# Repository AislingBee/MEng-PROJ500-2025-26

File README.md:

# MEng-PROJ500-2025-26

Main repository for the PROJ500 humanoid robot project.

Project timeline: December 2025 to May 2026.

## Start Here

1. Read this file for the project map.
2. Read [README_PROJECT_MAP.md](README_PROJECT_MAP.md) for a top-level file/folder map.
3. Read [README_IMPORTANT_PATHS.md](README_IMPORTANT_PATHS.md) for key entrypoints and files.
4. Read [README_QUICKSTART.md](README_QUICKSTART.md) for launch order and runtime checks.
5. For simulation and Isaac workflow, read [simulation/README.md](simulation/README.md).
6. For ROS2 motor stack, read [Software/src/motor_control/README.md](Software/src/motor_control/README.md).
7. For the RCU UDP protocol handover, read [Charlie/STM32Cube/Tools/ROS2/HANDOVER_INSTRUCTIONS.md](Charlie/STM32Cube/Tools/ROS2/HANDOVER_INSTRUCTIONS.md).

## Top-Level Repository Overview

## New STM32 Addition (RCU UDP Bridge)

The current hardware path now supports a direct STM32 RCU UDP binary bridge.

- New bridge node: [Software/src/motor_control/motor_control/bridges/rcu_udp_bridge.py](Software/src/motor_control/motor_control/bridges/rcu_udp_bridge.py)
- RCU launch entrypoint: [Software/src/motor_control/launch/rcu_launch.py](Software/src/motor_control/launch/rcu_launch.py)
- Full RL launch (with RCU transport): [Software/src/motor_control/launch/rl_robot_launch.py](Software/src/motor_control/launch/rl_robot_launch.py)
- Protocol reference and handover: [Charlie/STM32Cube/Tools/ROS2/HANDOVER_INSTRUCTIONS.md](Charlie/STM32Cube/Tools/ROS2/HANDOVER_INSTRUCTIONS.md)

RCU network defaults:

- RCU IP: `192.168.100.10`
- Thor host IP: `192.168.100.20/24`
- Telemetry in: UDP `7700`
- Command out: UDP `7701`
- Supervision out: UDP `7702`

The Software Nucleo bridge path has been removed; RCU UDP is now the primary integration path.

### Core folders

- [simulation](simulation): Isaac Sim assets, tools, and RL workspace.
  - Further docs:
  - [simulation/README.md](simulation/README.md)
  - [simulation/docs/README.md](simulation/docs/README.md)
  - [simulation/isaac/README.md](simulation/isaac/README.md)
  - [simulation/isaac/rl/README.md](simulation/isaac/rl/README.md)

- [Software](Software): software stack for firmware, bridge tools, ROS2 motor test package, and configs.
  - ROS2 motor package:
  - [Software/src/motor_control/README.md](Software/src/motor_control/README.md)
  - Integration guide:
  - [Software/ROS_STM32_INTEGRATION.md](Software/ROS_STM32_INTEGRATION.md)

### Top-level files

- [README.md](README.md): this overview.
- [joint_limit_results.csv](joint_limit_results.csv): saved joint limit validation/test output.
- [hardware/thor/thor_policy_runner.py](hardware/thor/thor_policy_runner.py): policy runtime script.
- [power_shell_commands](power_shell_commands): command notes and helper snippets.

## Software Folder Details

Within [Software](Software):

- [Software/config](Software/config): shared config files (including JSON config used by launch files).
- [Software/nucleo](Software/nucleo): motor protocol notes/manual assets and experimental scripts.
- [Software/src/motor_control](Software/src/motor_control): ROS2 package for command generation, bridges, listeners, and launch files.

## Important Readme and Documentation Index

### Simulation and RL

- [simulation/README.md](simulation/README.md)
- [simulation/docs/README.md](simulation/docs/README.md)
- [simulation/isaac/README.md](simulation/isaac/README.md)
- [simulation/isaac/rl/README.md](simulation/isaac/rl/README.md)

### Firmware and Bridge

- [Software/ROS_STM32_INTEGRATION.md](Software/ROS_STM32_INTEGRATION.md)
- [Charlie/STM32Cube/Tools/ROS2/HANDOVER_INSTRUCTIONS.md](Charlie/STM32Cube/Tools/ROS2/HANDOVER_INSTRUCTIONS.md)

### ROS2 Motor Test

- [Software/src/motor_control/README.md](Software/src/motor_control/README.md)
- Launch files are in [Software/src/motor_control/launch](Software/src/motor_control/launch).
- Test and bridge nodes are in [Software/src/motor_control/motor_control](Software/src/motor_control/motor_control).

## Contribution Rules

- Do not push directly to main.
- Use feature branches and open a pull request.
- Include a clear summary of changes and test steps in each PR.
- Merge to main only after review.
- Delete merged branches.

## Commit and PR Conventions

- Use descriptive commit titles (example: Add ROS2 joint command bridge).
- Include test evidence in PR descriptions.
- Provide exact run steps and expected output for reviewers.

Example test flow:

```bash
cd Software/src/motor_control
colcon build --packages-select motor_control
source install/setup.bash
ros2 launch motor_control rl_robot_launch.py
```

## Team

- Mechanical Lead (Project Lead): Brendan
- Electrical Lead: Charlie
- Simulation Lead: Joe
- Software/ROS Lead: Ash

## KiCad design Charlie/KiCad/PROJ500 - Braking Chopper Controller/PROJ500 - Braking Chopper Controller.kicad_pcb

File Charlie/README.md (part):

# PROJ500 Humanoid Robot — Charlie's Handover

**Author:** Charlie  
**Date:** May 2026  
**Project:** MEng PROJ500 — Plymouth Humanoid Robot  

This folder contains all hardware and firmware deliverables produced during the 2025–26 academic year. It is structured into three top-level areas:

```
Charlie/
├── KiCad/                  — PCB schematics and layouts (5 boards)
├── PROJ500_PDU_FPGA/       — Lattice MachXO2 FPGA project (PDU sequencer)
└── STM32Cube/              — STM32 firmware (PDU + RCU) and PC tools
```

---

## System Overview

The robot's electronic architecture is split across two custom boards:

| Board | MCU | Role |
|---|---|---|
| **PDU** — Power Distribution Unit | STM32G474 | Battery management, power sequencing, relay/contactor control via FPGA |
| **RCU** — Real-Time Control Unit | STM32H723 | Motor CAN buses, Ethernet UDP to Thor, dual IMU, PDU telemetry forwarding |

The PDU and RCU communicate over a dedicated **management CAN bus (250 kbps)**. The RCU talks to the Thor AI computer (Jetson/PC) over **UDP/Ethernet**. Motors are driven by the RCU over two **1 Mbps CAN buses** using the RobStride RS04 private protocol.

```
[ Battery ] → [ PDU ] ──CAN(250k)──→ [ RCU ] ──Ethernet(UDP)──→ [ Thor / ROS2 ]
                 ↑FPGA                    ↓ ↑
               sequencer              FDCAN1/3 (1Mbps)
                                    [ 12× RS04 Motors ]
```

---

## 1. KiCad — PCB Designs

All boards were designed in **KiCad**. Each folder contains the full KiCad project (`.kicad_sch`, `.kicad_pcb`, `.kicad_pro`), a rendered **PDF schematic**, exported **STEP** 3D model, **BOM** (bill of materials in `bom/`), and **Gerber/drill files** for fabrication in `production/`.

### 1.1 Power Distribution Board (PDU)

**Folder:** `KiCad/PROJ500 - Power Distribution Board/`

The most complex board. Manages all power rails from the battery pack and implements hardware safety logic.

**Key schematics:**
| Sub-sheet | File | Description |
|---|---|---|
| Top level | `PROJ500 - Power Distribution Board.kicad_sch` | Hierarchy root |
| MCU | `MCU.kicad_sch` | STM32G474 with FDCAN1 (management CAN), I2C4 (FPGA), UART3/4 (RS485, debug), ADC, SWD debug header |
| FPGA | `FPGA.kicad_sch` | Lattice MachXO2-256HC-5SG48C QFN48 — relay sequencer + I2C slave |
| Safety logic | `safety_logic.kicad_sch` | Hardware e-stop and overvoltage/undervoltage comparators feeding FPGA inputs |
| Comparators | `Comparators.kicad_sch` | OV/UV sense circuits |
| Coil driver | `Coil_Driver.kicad_sch` | Relay coil drive circuit (K_EN / K_SEL) |
| Aux outputs | `Aux_Outputs.kicad_sch` | Auxiliary 12 V/24 V switched outputs, buzzer, status LEDs |

**Power rails** — refer to `PROJ500 - Power Distribution Board.pdf` for the confirmed rail architecture and voltage levels.

**ADC channels (TLA2528, I2C, address 0x17):**
| CH | Signal | Scaling |
|---|---|---|
| 0 | V_VRAW | ÷31 |
| 1 | I_VRAW_SW | 9.47× shunt amp |
| 2 | V_12V_SW | ÷7.8 |
| 3 | V_24V_SW | ÷14 |
| 4 | I_12V_SW | 4× shunt amp |
| 5 | I_24V_SW | 4× shunt amp |
| 6 | THERM1 | NTC β-model |
| 7 | THERM2 | NTC β-model |

**Local STM32G474 ADC pins:**
| Pin | Signal |
|---|---|
| PA6 ADC2_CH3 | Board thermistor 0 |
| PA7 ADC2_CH4 | Board thermistor 1 |
| PC4 ADC2_CH5 | Board thermistor 2 |
| PB0 ADC1_CH15 | V_SOURCE (36.71× divider) |
| PB1 ADC1_CH12 | V_BUS (36.71× divider) |
| PB2 ADC2_CH12 | I_COIL (2× shunt amp, 10 mΩ / ×50) |

---

### 1.2 Real-Time Control Unit (RCU)

**Folder:** `KiCad/PROJ500 - Real-Time Control Unit/`

**Key schematics:**
| Sub-sheet | File | Description |
|---|---|---|
| MCU | `STM32_MCU.kicad_sch` | STM32H723VGT6, FDCAN1/2/3, SPI3/4 (IMUs), Ethernet RMII |
| Ethernet | `ETHERNET.kicad_sch` | RJ45 + magnetics |
| ETH PHY | `ETH_PHY.kicad_sch` | PHY chip (RMII mode) |
| IMU | `IMU.kicad_sch` | Dual LSM6DSOX IMUs on SPI3/4 |
| ESP32 | `ESP32_MCU.kicad_sch` | Co-processor / future wireless |

A **production-ready Gerber zip** (`PROJ500 - Real-Time Control Unit.zip`) is included for direct upload to a PCB manufacturer.

---

### 1.3 Power Supply Board

**Folder:** `KiCad/PROJ500 - Power Supply Board/`

Standalone DC-DC converter board providing regulated rails from a high-voltage input.

**Converters:**
| File | Part | Output |
|---|---|---|
| `AP62200 - 5V 2A.kicad_sch` | AP62200 | 5 V / 2 A |
| `MIC28517 - 12V 4A.kicad_sch` | MIC28517 | 12 V / 4 A |
| `MIC28517 - 24V 8A.kicad_sch` | MIC28517 | 24 V / 8 A |
| `SiC437 - 12V 8A.kicad_sch` | SiC437 | 12 V / 8 A (high efficiency) |
| `Hot Swap Switch.kicad_sch` | TPS249x | Hot-swap / inrush limiting |
| `Shunt Amplifiers.kicad_sch` | — | Current sense amps |
| `TLA2528 ADC.kicad_sch` | TLA2528 | 8-ch ADC for rail monitoring |

A **TPS249x design spreadsheet** (`TPS249x_8x_Design_Calculator_REV_B.xlsx`) is included for recalculating hot-swap component values.

---

### 1.4 Auxiliary IMU Board

**Folder:** `KiCad/PROJ500 - Auxillary IMU Board/`

Compact breakout board for a single IMU (e.g. LSM6DSOX). Intended for body segments that cannot fit the main RCU.

---

### 1.5 Braking Chopper Controller

**Folder:** `KiCad/PROJ500 - Braking Chopper Controller/`

Handles regenerative braking energy from motors. Dissipates or redirects back-EMF during deceleration to protect the bus capacitors.

---

## 2. PROJ500_PDU_FPGA — Lattice MachXO2 FPGA

**Tool required:** Lattice Diamond (tested with 3.13)  
**Device:** MachXO2-256HC-5SG48C (SG48C QFN48 package)  
**Clock:** Internal OSCH @ 2.08 MHz  

### 2.1 Source Files

| File | Description |
|---|---|
| `pdu_glue_mxo2.sv` | **Main production image** — full relay sequencing FSM + EFB I2C slave |
| `pdu_selftest_mxo2.sv` | **Board self-test image** — drives all outputs for PCB bring-up continuity checks |
| `PDU_EFB_I2C.v` / `.edn` | Lattice EFB I2C slave instantiation (auto-generated from Diamond IP) |
| `PROJ500_PDU_FPGA.lpf` | Pin Location File — maps all signal names to physical QFN48 pins |
| `PROJ500_PDU_FPGA.ldf` | Diamond project file |
| `pdu_glue_synth.sdc` | Timing constraints (2.08 MHz clock constraint) |
| `tb_pdu_glue.sv` | Simulation testbench for the main FSM |
| `tb_pdu_selftest_mxo2.sv` | Simulation testbench for the self-test image |
| `sim_do.do` | ModelSim run script |

### 2.2 FPGA State Machine

The FPGA implements the main contactor and precharge relay sequencer:

| State | STATE_CODE | Description |
|---|---|---|
| ST_IDLE | 0 | All outputs de-asserted, waiting for SW_COMPUTE |
| ST_COMPUTE | 3 | SW_COMPUTE=1, awaiting arm permission |
| ST_PRECHARGE | 1 | Relay closed on NC (precharge) path; charging bus |
| ST_PRECHARGE_ABORT | 1 | Relay held closed while bus discharges safely |
| ST_ARMED | 2 | Main contactor closed, motors active |
| ST_FAULT | 0 | Latched fault — requires manual SW_RST_FAULT |

**Relay control note:** `K_SEL=0` selects the **precharge (NC) path**; `K_SEL=1` selects the **dump path**. Always verify polarity on the bench before first energisation.

### 2.3 FPGA I2C Register Map

The FPGA exposes a read-only I2C slave at **address 0x55** (7-bit):

| Register | Address | Description |
|---|---|---|
| STATUS0 | 0x00 | Fault/status flags bitmask |
| FAULT_CODE | 0x01 | Fault reason code |
| STATE_CODE | 0x02 | FSM state (0=IDLE, 1=PCHG, 2=ARMED, 3=COMPUTE) |
| ACTIONS | 0x03 | Current output action register |
| INPUTS | 0x04 | Latched input states (e-stop, arm flags) |
| PCHG_HI | 0x05 | Precharge timer high byte |
| PCHG_LO | 0x06 | Precharge timer low byte |
| VERSION | 0x7F | FPGA firmware version |

### 2.4 Built Implementations

Two ready-to-program bitfiles are included:

| Implementation | Folder | Bitfile | JEDEC |
|---|---|---|---|
| Production (V1) | `V1/` | `PROJ500_PDU_FPGA_V1.bit` | `PROJ500_PDU_FPGA_V1.jed` |
| Self-test | `SELFTEST/` | `PROJ500_PDU_FPGA_SELFTEST.bit` | `PROJ500_PDU_FPGA_SELFTEST.jed` |

### 2.5 FPGA JTAG Programming (FT2232H)

Connect a FT2232H development board to the FPGA JTAG header (02×05 IDC):

| IDC Pin | Signal | FT2232H (ADBUS) |
|---|---|---|
| 1 | TCK | ADBUS0 |
| 2 | GND | GND |
| 3 | TMS | ADBUS3 |
| 4 | GND | GND |
| 5 | TDI | ADBUS1 |
| 6 | 3V3 | 3V3 |
| 7 | TDO | ADBUS2 |
| 8 | GND | GND |

Use Diamond Programmer or `openFPGALoader` with the `.jed` or `.bit` file.

---

## 3. STM32Cube — Firmware and Tools

### 3.1 MCU_PDU_V1 — PDU Firmware

**Target:** STM32G474RET6 (LQFP64)  
**IDE:** STM32CubeIDE  
**Project file:** `STM32Cube/MCU_PDU_V1/MCU_PDU_V1.ioc`  

The PDU runs a **bare-metal superloop** (no RTOS). All modules expose an `_init()` / `_tick()` API called from `pdu_app.c`.

#### Source Modules

| File | Description |
|---|---|
| `main.c` | CubeMX-generated HAL init; calls `PDU_App_Init()` then loops `PDU_App_Task()` |
| `pdu_app.c` | Superloop coordinator — sequences all subsystem ticks |
| `fpga_mon.c` | Polls FPGA I2C registers every ~50 ms; caches in `fpga_snapshot_t` |
| `pdu_adc.c` | Samples TLA2528 (I2C4, ext ADC) and local STM32 ADC channels |
| `ssd_energy.c` | Queries SSD RS485 energy meter over USART3 at 19200 baud (~5 Hz) |
| `pdu_mcan_app.c` | Management CAN TX/RX on FDCAN1 (250 kbps); sends telemetry to RCU |
| `pdu_selftest_cli_v3.c` | UART self-test CLI (build-mode selectable) |

#### Management CAN Frame IDs (PDU → RCU)

| CAN ID | Rate | Content |
|---|---|---|
| 0x511 | 2 Hz | PDU heartbeat |
| 0x520 | 10 Hz | FPGA status (status0, fault, state, actions, inputs, version, pchg) |
| 0x521 | 10 Hz | Power rail voltages (V_RAW, 12 V, 24 V) |
| 0x522 | 10 Hz | Rail currents + thermistors |
| 0x523 | 5 Hz | SSD energy meter (I, V, P, T) |
| 0x524 | 10 Hz | Local ADC A (board therms 0–2, V_SOURCE) |
| 0x525 | 10 Hz | Local ADC B (V_BUS, I_COIL) |

**RCU → PDU:**

| CAN ID | Content |
|---|---|
| 0x530 | AUX switch command (bits[2:0]=CH3/2/1, bit3=buzz, bit4=LED blink) |
| 0x531 | CMD_FAULT request (bit0=assert, bit1=clear) |

#### STLink Debug Header (02×05 IDC)

| IDC Pin | Signal | Wire colour |
|---|---|---|
| 1 | 3.3 V | Red |
| 2 | SWDIO | Yellow |
| 3 | GND | Black |
| 4 | SWCLK | Green |
| 5 | GND | Black |
| 6 | SWO | Blue |
| 7 | UART_RX | Brown |
| 8 | UART_TX | Grey |
| 9 | 5 V | Purple |
| 10 | NRST | White |

---

### 3.2 MCU_RCU_V1 — RCU Firmware

**Target:** STM32H723VGT6 (LQFP100)  
**IDE:** STM32CubeIDE  
**Project file:** `STM32Cube/MCU_RCU_V1/MCU_RCU_V1.ioc`  

Also a **bare-metal superloop**. All modules expose `_init()` / `_tick()` called from `rcu_app.c`.

#### Source Modules

| File | Description |
|---|---|
| `main.c` | HAL init; calls `RCU_App_Init()` then loops `RCU_App_Task()` |
| `rcu_app.c` | Superloop coordinator; scheduling buckets at 10 Hz and 200 Hz |
| `motor_bus.c` | FDCAN1 (right) + FDCAN3 (left) motor CAN; drains RX FIFOs, caches feedback |
| `rs04.c` | RobStride RS04 CAN codec — pure, no HAL dependency |
| `imu.c` | Dual LSM6DSOX on SPI3/4 at 416 Hz ODR; DRDY interrupt driven |
| `eth_udp.c` | lwIP raw-API UDP sockets; TX/RX on ports 7700/7701/7702 |
| `mcan_pdu.c` | Receives PDU telemetry over FDCAN2 (management CAN); caches in `pdu_telem_t` |
| `telem_pack.c` | Assembles UDP packets from live subsystem data; dispatches inbound motor commands |
| `rcu_pkt.h` | All UDP packet type definitions and structs (source of truth for the protocol) |
| `rcu_selftest_cli_v1.c` | UART self-test CLI |

#### Motor Bus Mapping (12-DOF Lower Body)

| Motor ID | Joint | Bus |
|---|---|---|
| 1 | pelvis_link_l_yaw_joint | LEFT (FDCAN3) |
| 2 | pelvis_link_r_yaw_joint | RIGHT (FDCAN1) |
| 3 | l_hip_yaw_link_l_pitch_joint | LEFT |
| 4 | r_hip_yaw_link_r_pitch_joint | RIGHT |
| 5 | l_hip_pitch_link_l_roll_joint | LEFT |
| 6 | r_hip_pitch_link_r_roll_joint | RIGHT |
| 7 | l_thigh_link_l_knee_joint | LEFT |
| 8 | r_thigh_link_r_knee_joint | RIGHT |
| 9 | l_shank_link_l_ankle_joint | LEFT |
| 10 | r_shank_link_r_ankle_joint | RIGHT |
| 11 | l_ankle_link_l_foot_joint | LEFT |
| 12 | r_ankle_link_r_foot_joint | RIGHT |

#### IMU Configuration

| | IMU0 | IMU1 |
|---|---|---|
| SPI bus | SPI4 (PE2/5/6) | SPI3 (PC10/11/12) |
| Chip Select | PC13 | PA15 |
| DRDY / INT1 | PE3 (EXTI3) | PA9 (EXTI9_5) |
| ODR | 416 Hz | 416 Hz |
| Accel range | ±4 g (0.122 mg/LSB) | same |
| Gyro range | ±500 dps (17.5 mdps/LSB) | same |
| Temp | raw/256 + 25 → °C | same |

#### Network Configuration

| Parameter | Value |
|---|---|
| RCU static IP | `192.168.100.10` |
| Thor IP | `192.168.100.20` |
| Subnet mask | `255.255.255.0` |
| Telem TX port (RCU→Thor) | 7700 |
| Cmd RX port (Thor→RCU) | 7701 |
| Supervision TX port (RCU→Thor) | 7702 |

---

### 3.3 UDP Binary Protocol Reference

Full detail is in `STM32Cube/MCU_RCU_V1/THOR_INTERFACE.md` and `STM32Cube/Tools/ROS2/HANDOVER_INSTRUCTIONS.md`. Summary below.

**Packet header (6 bytes, all packets):**
```
[0:1]  magic  = 0x5243  ('RC' little-endian)
[2]    type   — see below
[3]    seq    — rolling 0–255
[4:5]  len    — payload bytes (LE uint16)
```

**Packet types:**

| Type | Direction | Rate | Description |
|---|---|---|---|
| 0x01 | RCU → Thor | 10 Hz | Slow telemetry (PDU power, therms, SSD, IMU) — 72 bytes |
| 0x02 | RCU → Thor | 200 Hz | Motor feedback (pos, vel, torque, error) — 4 + n×10 bytes |
| 0x03 | RCU → Thor | on-change | Supervision events |
| 0x04 | RCU → Thor | 200 Hz | Fast IMU packet (28 bytes) — **primary RL loop IMU source** |
| 0x10 | Thor → RCU | 200 Hz | Motor command (n × 10 bytes) |
| 0x11 | Thor → RCU | on-demand | Motor supervisory (enable mask, ctrl_mode, fault clear) |
| 0x20 | Thor → RCU | on-demand | Debug command (ping, buzz, LED, CAN loopback, soft reset, etc.) |
| 0x21 | RCU → Thor | on-demand | Debug reply |

**Motor command encoding (uint16 on wire):**
```
value_raw = int((value - min) / (max - min) * 65535)
```
| Quantity | Min | Max |
|---|---|---|
| Position | −12.57 rad | +12.57 rad |
| Velocity | −15 rad/s | +15 rad/s |
| Torque | −120 N·m | +120 N·m |

Mid-scale (32767) = zero for position, velocity, and torque.

**Motor supervisory packet (Type 0x11) — enable all motors in CSP mode:**
```python
import struct
payload = struct.pack("<HHBxxx", 0x0FFF, 0x0FFF, 1)  # enable + CSP
```

**Full e-stop:**
```python
payload = struct.pack("<HHBxxx", 0x0000, 0x0000, 1)
```

---

### 3.4 Shared Library

**Folder:** `STM32Cube/Shared/`

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
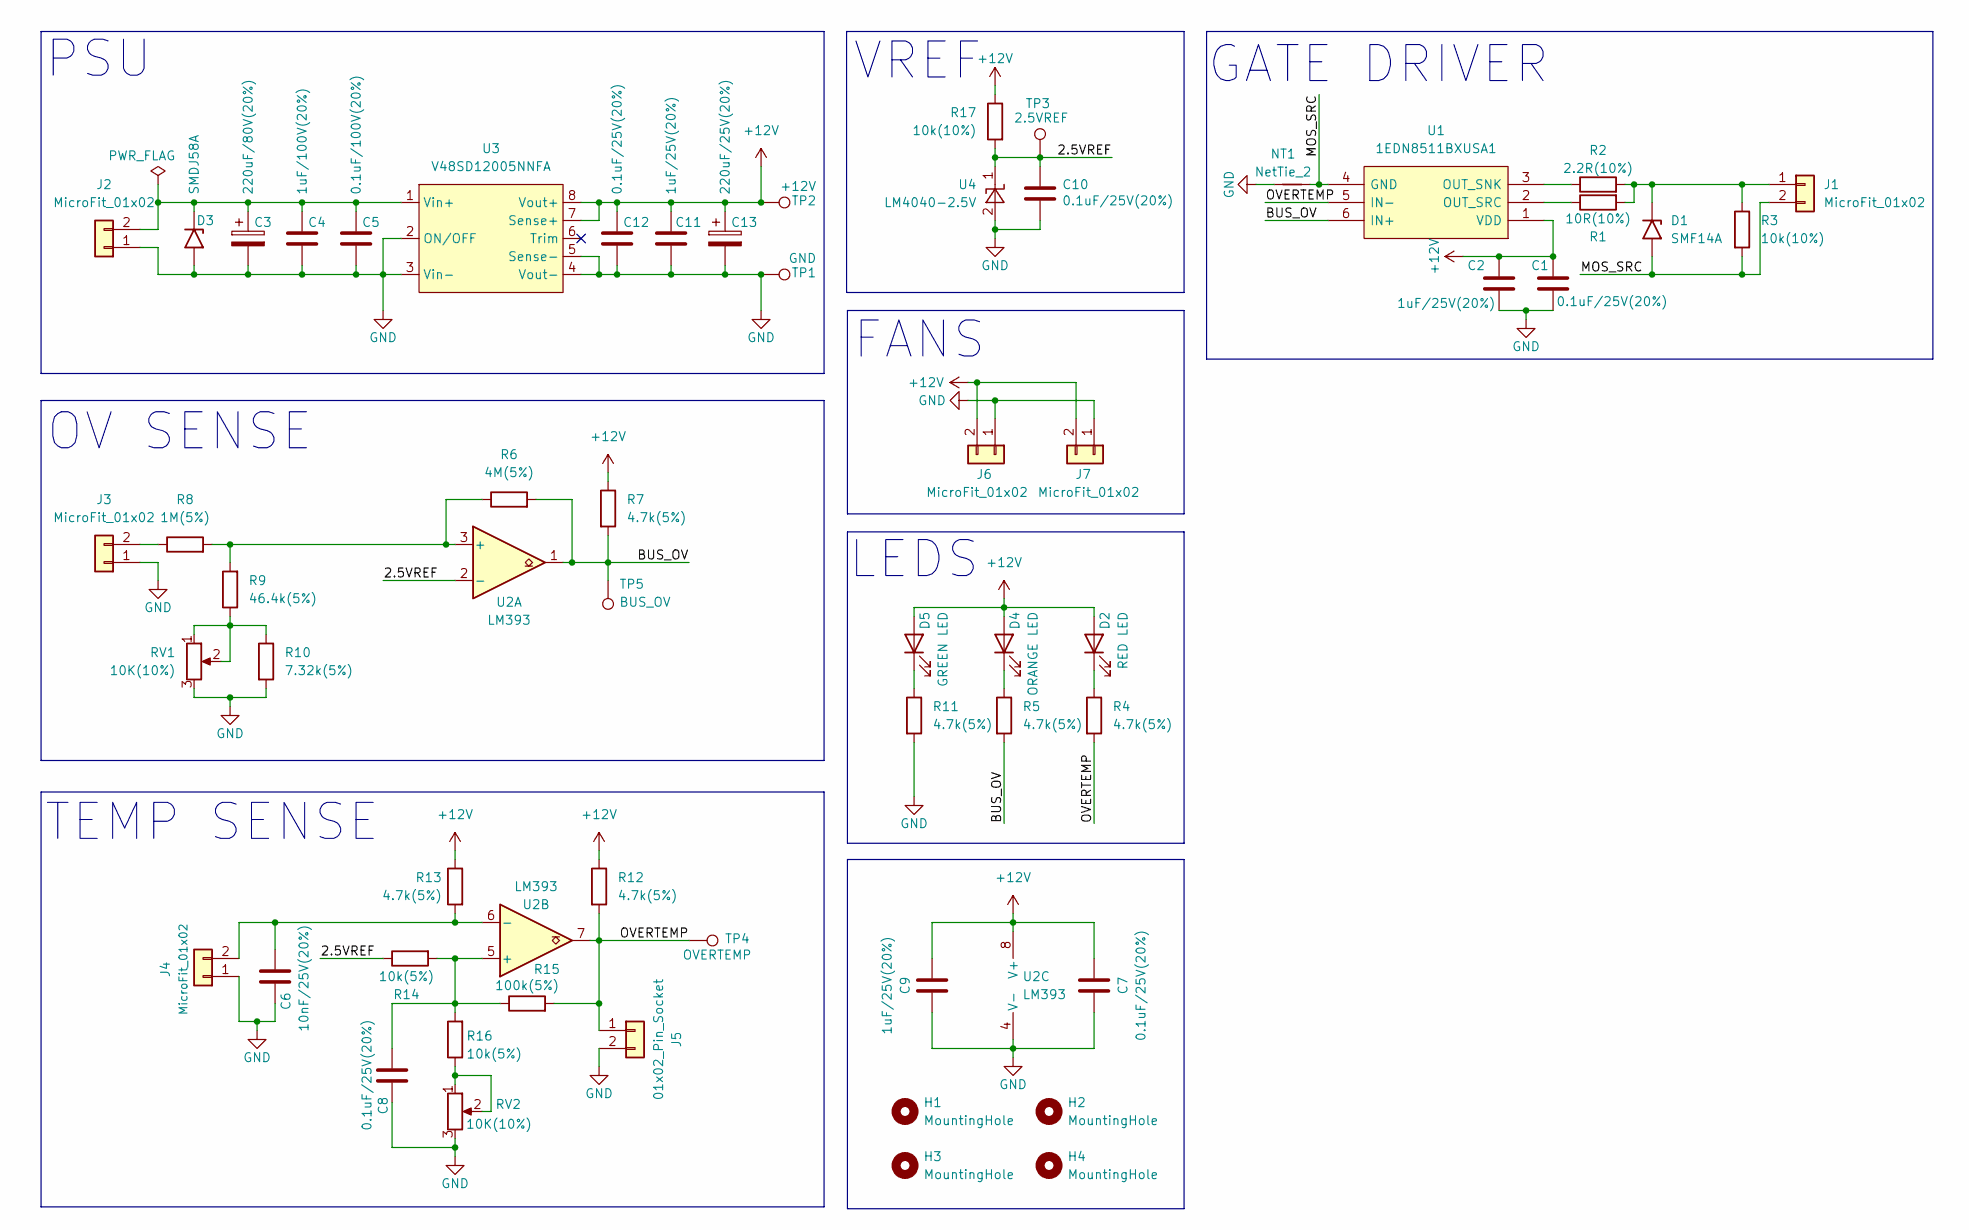
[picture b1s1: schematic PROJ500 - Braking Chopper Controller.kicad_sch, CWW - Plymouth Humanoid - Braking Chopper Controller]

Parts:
C1, C7, C8, C10, C12: 0.1uF/25V(20%); C_0402_1005Metric
C2, C9, C11: 1uF/25V(20%); C_0603_1608Metric
C3: 220uF/80V(20%); CP_Radial_D12.5mm_P5.00mm
C4: 1uF/100V(20%); C_0603_1608Metric
C5: 0.1uF/100V(20%); C_0603_1608Metric
C6: 10nF/25V(20%); C_0402_1005Metric
C13: 220uF/25V(20%); CP_Radial_D12.5mm_P5.00mm
D1: SMF14A; D_SMF
D2: RED LED; LED_D5.0mm
D3: SMDJ58A; D_SMC
D4: ORANGE LED; LED_D5.0mm
D5: GREEN LED; LED_D5.0mm
H1, H2, H3, H4: MountingHole; MountingHole_3.2mm_M3
J1, J2, J3, J4, J6, J7: MicroFit_01x02; Molex_Micro-Fit_3.0_43650-0215_1x02_P3.00mm_Vertical
J5: 01x02_Pin_Socket; PinHeader_1x02_P2.54mm_Vertical
NT1: NetTie_2; NetTie-2_SMD_Pad0.5mm
R1: 10R(10%); R_0402_1005Metric
R2: 2.2R(10%); R_0402_1005Metric
R3, R17: 10k(10%); R_0402_1005Metric
R4, R5, R7, R11, R12, R13: 4.7k(5%); R_0402_1005Metric
R6: 4M(5%); R_0402_1005Metric
R8: 1M(5%); R_0603_1608Metric
R9: 46.4k(5%); R_0402_1005Metric
R10: 7.32k(5%); R_0402_1005Metric
R14, R16: 10k(5%); R_0402_1005Metric
R15: 100k(5%); R_0402_1005Metric
RV1, RV2: 10K(10%); Potentiometer_Bourns_3296W_Vertical
TP1: GND; TestPoint_Pad_D1.5mm
TP2: +12V; TestPoint_Pad_D1.5mm
TP3: 2.5VREF; TestPoint_Pad_D1.5mm
TP4: OVERTEMP; TestPoint_Pad_D1.5mm
TP5: BUS_OV; TestPoint_Pad_D1.5mm
U1: 1EDN8511BXUSA1; SOT95P280X145-6N; Mouser Part Number 726-1EDN8511BXUSA1
U2: LM393; TSSOP-8_4.4x3mm_P0.65mm
U3: V48SD12005NNFA
U4: LM4040-2.5V; SOT-23-3; Part Number LM4040B25FTA

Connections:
+12V: C1.2, C2.1, C7.1, C9.1, C11.1, C12.1, C13.1, D2.2 (A), D4.2 (A), D5.2 (A), J6.2, J7.2, R7.1, R12.1, R13.1, R17.1, TP2.1, U1.1 (VDD), U2.8 (V+), U3.7 (Sense+), U3.8 (Vout+)
/2.5VREF: C10.1, R14.1, R17.2, TP3.1, U2.2 (-), U4.1 (K)
/BUS_OV: R5.2, R6.2, R7.2, TP5.1, U1.6 (IN+), U2.1
/MOS_SRC: D1.2 (A2), J1.2, NT1.2, R3.2, U1.4 (GND)
/OVERTEMP: J5.1, R4.2, R12.2, R15.2, TP4.1, U1.5 (IN-), U2.7
GND: C1.1, C2.2, C3.2, C4.2, C5.2, C6.2, C7.2, C8.2, C9.2, C10.2, C11.2, C12.2, C13.2, D3.2 (A2), J2.1, J3.1, J4.1, J5.2, J6.1, J7.1, NT1.1, R10.2, R11.2, RV1.3, RV2.3, TP1.1, U2.4 (V-), U3.2 (ON/OFF), U3.3 (Vin-), U3.4 (Vout-), U3.5 (Sense-), U4.2 (A)
unnamed: D1.1 (A1), J1.1, R1.2, R2.2, R3.1
unnamed: D2.1 (K), R4.1
unnamed: C3.1, C4.1, C5.1, D3.1 (A1), J2.2, U3.1 (Vin+)
unnamed: D4.1 (K), R5.1
unnamed: D5.1 (K), R11.1
unnamed: J3.2, R8.1
unnamed: C6.1, J4.2, R13.2, U2.6 (-)
unnamed: R9.1, R10.1, RV1.1, RV1.2
unnamed: R16.1, RV2.1, RV2.2
unnamed: R2.1, U1.3 (OUT_SNK)
unnamed: R1.1, U1.2 (OUT_SRC)
unnamed: R6.1, R8.2, R9.2, U2.3 (+)
unnamed: C8.1, R14.2, R15.1, R16.2, U2.5 (+)

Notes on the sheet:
OV SENSE
GATE DRIVER
TEMP SENSE
VREF
LEDS
FANS
PSU

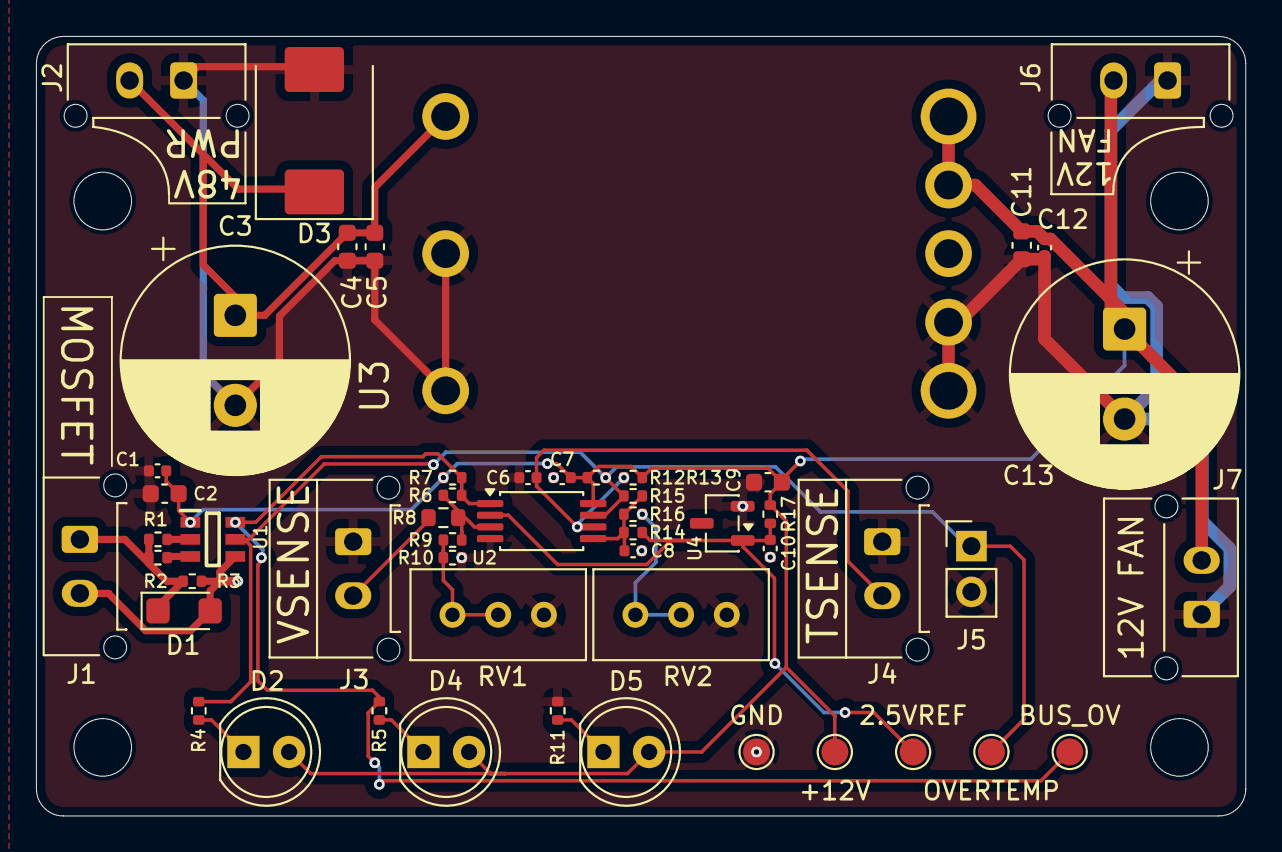
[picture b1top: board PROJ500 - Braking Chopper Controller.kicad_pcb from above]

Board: 2 copper layers, 67.2 x 43.3 mm, 58 parts (0 on the bottom side), 19 nets.

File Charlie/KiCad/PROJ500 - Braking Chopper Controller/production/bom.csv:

Designator,Footprint,Quantity,Value,LCSC Part #
"C1, C10, C12, C7, C8",0402,5,0.1uF/25V(20%),
"C11, C2, C9",0603,3,1uF/25V(20%),
C13,CP_Radial_D12.5mm_P5.00mm,1,220uF/25V(20%),
C3,CP_Radial_D12.5mm_P5.00mm,1,220uF/80V(20%),
C4,0603,1,1uF/100V(20%),
C5,0603,1,0.1uF/100V(20%),
C6,0402,1,10nF/25V(20%),
D1,D_SMF,1,SMF14A,
D2,LED_D5.0mm,1,RED LED,
D3,D_SMC,1,SMDJ58A,
D4,LED_D5.0mm,1,ORANGE LED,
D5,LED_D5.0mm,1,GREEN LED,
"J1, J2, J3, J4, J6, J7",Molex_Micro-Fit_3.0_43650-0215_1x02_P3.00mm_Vertical,6,MicroFit_01x02,
J5,PinHeader_1x02_P2.54mm_Vertical,1,01x02_Pin_Socket,
R1,0402,1,10R(10%),
R10,0402,1,7.32k(5%),
"R11, R12, R13, R4, R5, R7",0402,6,4.7k(5%),
"R14, R16",0402,2,10k(5%),
R15,0402,1,100k(5%),
"R17, R3",0402,2,10k(10%),
R2,0402,1,2.2R(10%),
R6,0402,1,4M(5%),
R8,0603,1,1M(5%),
R9,0402,1,46.4k(5%),
"RV1, RV2",Potentiometer_Bourns_3296W_Vertical,2,10K(10%),
TP1,TestPoint_Pad_D1.5mm,1,GND,
TP2,TestPoint_Pad_D1.5mm,1,+12V,
TP3,TestPoint_Pad_D1.5mm,1,2.5VREF,
TP4,TestPoint_Pad_D1.5mm,1,OVERTEMP,
TP5,TestPoint_Pad_D1.5mm,1,BUS_OV,
U1,SOT95P280X145-6N,1,1EDN8511BXUSA1,
U2,TSSOP-8_4.4x3mm_P0.65mm,1,LM393,
U3,V48SD12005NNFA,1,V48SD12005NNFA,
U4,SOT-23-3,1,LM4040-2.5V,

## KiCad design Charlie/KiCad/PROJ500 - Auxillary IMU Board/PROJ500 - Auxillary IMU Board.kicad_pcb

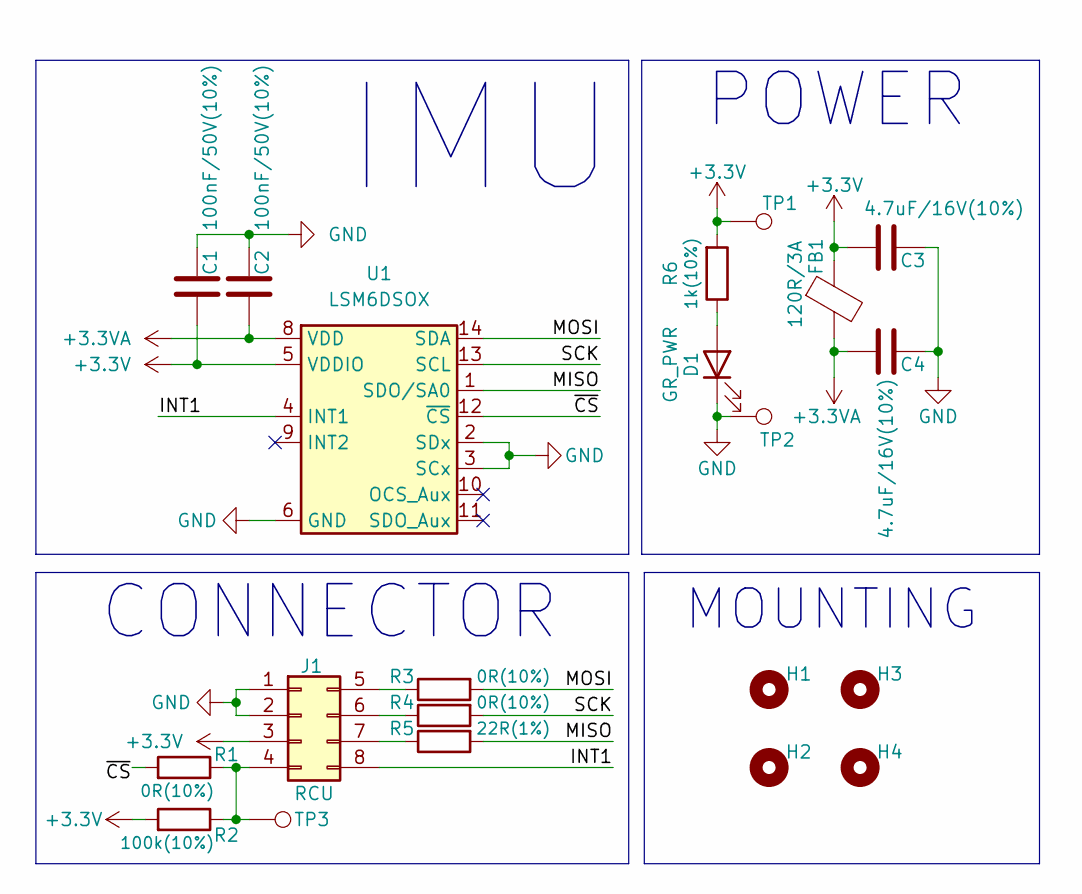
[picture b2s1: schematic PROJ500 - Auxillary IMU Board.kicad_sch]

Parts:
C1, C2: 100nF/50V(10%); C_0402_1005Metric
C3, C4: 4.7uF/16V(10%); C_0805_2012Metric
D1: GR_PWR; D_0805_2012Metric
FB1: 120R/3A; L_0603_1608Metric
H1, H2, H3, H4: MountingHole; MountingHole_3.2mm_M3
J1: RCU; Molex_Micro-Fit_3.0_43045-0812_2x04_P3.00mm_Vertical
R1, R3, R4: 0R(10%); R_0402_1005Metric
R2: 100k(10%); R_0402_1005Metric
R5: 22R(1%); R_0402_1005Metric
R6: 1k(10%); R_0402_1005Metric
TP1, TP2, TP3: TestPoint; TestPoint_Pad_D1.0mm
U1: LSM6DSOX; ST_LGA-14L_2.5x3.0mm_P0.5mm_4x3

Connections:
+3.3V: C1.1, C3.2, FB1.1, J1.3, R2.2, R6.2, TP1.1, U1.5 (VDDIO)
+3.3VA: C2.1, C4.2, FB1.2, U1.8 (VDD)
/INT1: J1.8, U1.4 (INT1)
/MISO: R5.2, U1.1 (SDO/SA0)
/MOSI: R3.2, U1.14 (SDA)
/SCK: R4.2, U1.13 (SCL)
/~CS: R1.2, U1.12 (~CS)
GND: C1.2, C2.2, C3.1, C4.1, D1.1 (K), J1.1, J1.2, TP2.1, U1.2 (SDx), U1.3 (SCx), U1.6 (GND), U1.7 (GND)
unnamed: D1.2 (A), R6.1
unnamed: J1.4, R1.1, R2.1, TP3.1
unnamed: J1.5, R3.1
unnamed: J1.6, R4.1
unnamed: J1.7, R5.1

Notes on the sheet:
POWER
IMU
MOUNTING
CONNECTOR

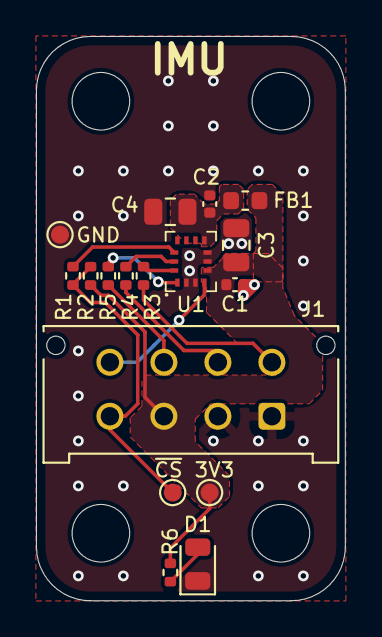
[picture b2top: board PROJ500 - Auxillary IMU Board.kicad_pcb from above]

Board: 2 copper layers, 17.2 x 31.4 mm, 21 parts (0 on the bottom side), 13 nets.

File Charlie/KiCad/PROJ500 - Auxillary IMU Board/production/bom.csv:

Designator,Footprint,Quantity,Value,LCSC Part #
"C1, C2",0402,2,100nF/50V(10%),
"C3, C4",0805,2,4.7uF/16V(10%),
D1,0805,1,GR_PWR,
FB1,0603,1,120R/3A,
J1,Molex_Micro-Fit_3.0_43045-0812_2x04_P3.00mm_Vertical,1,RCU,
"R1, R3, R4",0402,3,0R(10%),
R2,0402,1,100k(10%),
R5,0402,1,22R(1%),
R6,0402,1,1k(10%),
"TP1, TP2, TP3",TestPoint_Pad_D1.0mm,3,TestPoint,
U1,ST_LGA-14L_2.5x3.0mm_P0.5mm_4x3,1,LSM6DSOX,

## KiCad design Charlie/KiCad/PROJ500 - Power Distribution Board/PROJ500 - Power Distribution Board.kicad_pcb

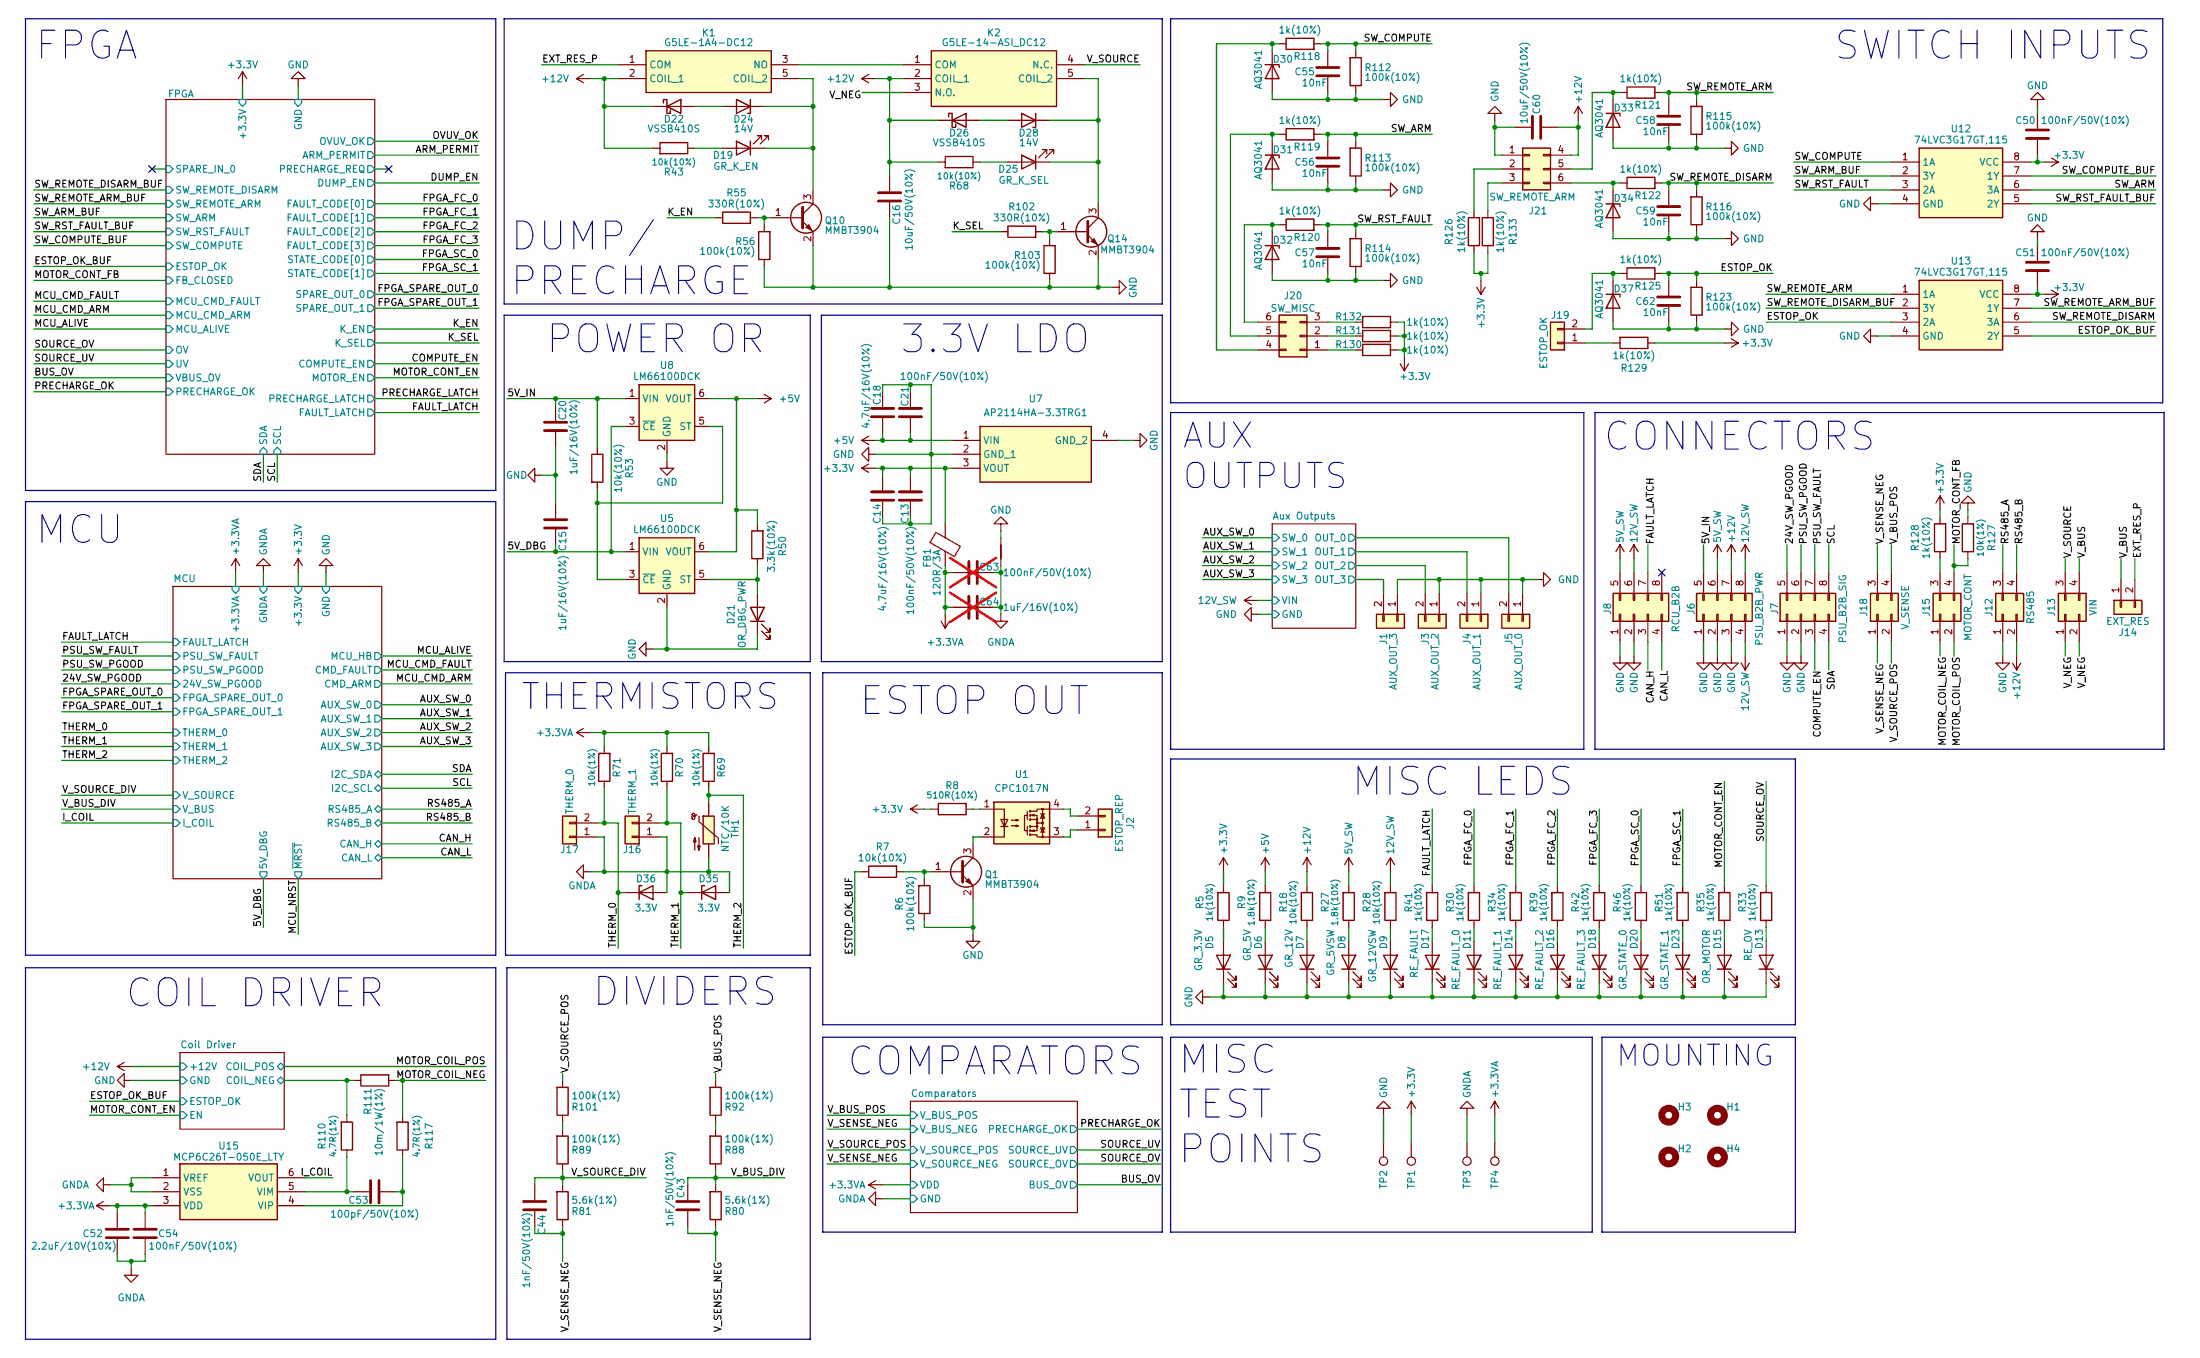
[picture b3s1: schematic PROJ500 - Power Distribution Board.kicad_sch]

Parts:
C13, C21, C50, C51, C54: 100nF/50V(10%); C_0402_1005Metric
C14, C18: 4.7uF/16V(10%); C_0805_2012Metric
C15, C20: 1uF/16V(10%); C_0603_1608Metric
C16, C60: 10uF/50V(10%); C_1206_3216Metric
C43, C44: 1nF/50V(10%); C_0402_1005Metric
C52: 2.2uF/10V(10%); C_0603_1608Metric
C53: 100pF/50V(10%); C_0402_1005Metric
C55, C56, C57, C58, C59, C62: 10nF/50V(10%); C_0402_1005Metric
C63: 100nF/50V(10%); C_0402_1005Metric; not fitted
C64: 1uF/16V(10%); C_0603_1608Metric; not fitted
D5: GR_3.3V; D_0805_2012Metric
D6: GR_5V; D_0805_2012Metric
D7: GR_12V; D_0805_2012Metric
D8: GR_5VSW; D_0805_2012Metric
D9: GR_12VSW; D_0805_2012Metric
D11: RE_FAULT_0; D_0805_2012Metric
D13: RE_OV; D_0805_2012Metric
D14: RE_FAULT_1; D_0805_2012Metric
D15: OR_MOTOR; D_0805_2012Metric
D16: RE_FAULT_2; D_0805_2012Metric
D17: RE_FAULT; D_0805_2012Metric
D18: RE_FAULT_3; D_0805_2012Metric
D19: GR_K_EN; D_0805_2012Metric
D20: GR_STATE_0; D_0805_2012Metric
D21: OR_DBG_PWR; D_0805_2012Metric
D22, D26: VSSB410S; D_SMB
D23: GR_STATE_1; D_0805_2012Metric
D24, D28: 14V; D_SOD-123
D25: GR_K_SEL; D_0805_2012Metric
D30, D31, D32, D33, D34, D37: AQ3041; D_SOD-882
D35, D36: 3.3V; D_SOD-123
FB1: 120R/3A; L_0603_1608Metric
H1, H2, H3, H4: MountingHole; MountingHole_3.2mm_M3
J1: AUX_OUT_3; TBP02R138102BE
J2: ESTOP_REP; TBP02R138102BE
J3: AUX_OUT_2; TBP02R138102BE
J4: AUX_OUT_1; TBP02R138102BE
J5: AUX_OUT_0; TBP02R138102BE
J6: PSU_B2B_PWR; Molex_Micro-Fit_3.0_43045-0800_2x04_P3.00mm_Horizontal
J7: PSU_B2B_SIG; Molex_Micro-Fit_3.0_43045-0800_2x04_P3.00mm_Horizontal
J8: RCU_B2B; Molex_Micro-Fit_3.0_43045-0800_2x04_P3.00mm_Horizontal
J12: RS485; Molex_Micro-Fit_3.0_43045-0400_2x02_P3.00mm_Horizontal
J13: VIN; Molex_Micro-Fit_3.0_43045-0400_2x02_P3.00mm_Horizontal
J14: EXT_RES; Molex_Micro-Fit_3.0_43045-0200_2x01_P3.00mm_Horizontal
J15: MOTOR_CONT; Molex_Micro-Fit_3.0_43045-0400_2x02_P3.00mm_Horizontal
J16: THERM_1; Molex_Micro-Fit_3.0_43045-0200_2x01_P3.00mm_Horizontal
J17: THERM_0; Molex_Micro-Fit_3.0_43045-0200_2x01_P3.00mm_Horizontal
J18: V_SENSE; Molex_Micro-Fit_3.0_43045-0400_2x02_P3.00mm_Horizontal
J19: ESTOP_OK; Molex_Micro-Fit_3.0_43045-0200_2x01_P3.00mm_Horizontal
J20: SW_MISC; Molex_Micro-Fit_3.0_43045-0600_2x03_P3.00mm_Horizontal
J21: SW_REMOTE_ARM; Molex_Micro-Fit_3.0_43045-0600_2x03_P3.00mm_Horizontal
K1: G5LE-1A4-DC12; G5LE1A4DC12; Mouser Part Number 653-G5LE-1A4-DC12
K2: G5LE-14-ASI_DC12; G5LE-14_SPDT; Mouser Part Number 653-G5LE-14-ASIDC12
NT1: NetTie_2; NetTie-2_SMD_Pad0.5mm
Q1, Q10, Q14: MMBT3904; SOT-23
R5, R30, R33, R34, R35, R39, R41, R42, R46, R51, R118, R119, R120, R121, R122, R125, R126, R128, R129, R130, R131, R132, R133: 1k(10%); R_0402_1005Metric
R6, R56, R103, R112, R113, R114, R115, R116, R123: 100k(10%); R_0402_1005Metric
R7, R18, R28, R43, R53, R68: 10k(10%); R_0402_1005Metric
R8: 510R(10%); R_0402_1005Metric
R9, R27: 1.8k(10%); R_0402_1005Metric
R50: 3.3k(10%); R_0402_1005Metric
R55, R102: 330R(10%); R_0402_1005Metric
R69, R70, R71, R127: 10k(1%); R_0402_1005Metric
R80, R81: 5.6k(1%); R_0402_1005Metric
R88, R89, R92, R101: 100k(1%); R_0603_1608Metric
R110, R117: 4.7R(1%); R_0402_1005Metric
R111: 10m/1W(1%); R_2512_6332Metric
TH1: NTC/10K; R_0402_1005Metric
TP1, TP2, TP3, TP4: TestPoint; TestPoint_Pad_D1.0mm
U1: CPC1017N; SOP-4_3.8x4.1mm_P2.54mm
U5, U8: LM66100DCK; SOT-363_SC-70-6
U7: AP2114HA-3.3TRG1; SOT-223; Mouser Part Number 621-AP2114HA-3.3TRG1
U12, U13: 74LVC3G17GT,115; XC7WT14GT115; Mouser Part Number 771-LVC3G17GT115
U15: MCP6C26T-050E_LTY; SOT-363_SC-70-6; Manufacturer_Part_Number MCP6C26T-050E/LTY

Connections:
5V_SW: J6.6, J8.5, R27.2
12V_SW: J6.4, J6.8, J8.6, R28.2; also elsewhere on the board
+3.3V: C13.1, C14.2, C50.1, C51.1, FB1.1, R5.2, R8.1, R126.1, R128.2, R129.1, R130.1, R131.1, R132.1, R133.1, TP1.1, U7.3 (VOUT), U12.8 (VCC), U13.8 (VCC); also elsewhere on the board
+3.3VA: C52.1, C54.1, C63.1, C64.2, FB1.2, R69.2, R70.2, R71.2, TP4.1, U15.3 (VDD); also elsewhere on the board
+5V: C18.2, C21.1, R9.2, R50.2, U5.6 (VOUT), U7.1 (VIN), U8.6 (VOUT)
+12V: C16.2, C60.2, D22.1 (K), D26.1 (K), J6.7, J12.2, J21.4, K1.2 (COIL_1), K2.2 (COIL_1), R18.2, R43.2, R68.2; also elsewhere on the board
/5V_DBG: C15.2, U5.1 (VIN), U8.3 (~CE); also elsewhere on the board
/5V_IN: C20.1, J6.5, R53.1, U8.1 (VIN)
/24V_SW_PGOOD: J7.5; also elsewhere on the board
/Aux Outputs/OUT_0: J5.2; also elsewhere on the board
/Aux Outputs/OUT_1: J4.2; also elsewhere on the board
/Aux Outputs/OUT_2: J3.2; also elsewhere on the board
/Aux Outputs/OUT_3: J1.2; also elsewhere on the board
/CAN_H: J8.3; also elsewhere on the board
/CAN_L: J8.4; also elsewhere on the board
/COMPUTE_EN: J7.3; also elsewhere on the board
/Coil Driver/COIL_NEG: R110.2, R111.1; also elsewhere on the board
/ESTOP_OK: C62.1, R123.2, R125.2, U13.3 (2A)
/ESTOP_OK_BUF: R7.1, U13.5 (2Y); also elsewhere on the board
/EXT_RES_P: J14.2, K1.1 (COM)
/FAULT_LATCH: J8.7, R41.2; also elsewhere on the board
/FPGA_FC_0: R30.2; also elsewhere on the board
/FPGA_FC_1: R34.2; also elsewhere on the board
/FPGA_FC_2: R39.2; also elsewhere on the board
/FPGA_FC_3: R42.2; also elsewhere on the board
/FPGA_SC_0: R46.2; also elsewhere on the board
/FPGA_SC_1: R51.2; also elsewhere on the board
/I_COIL: U15.6 (VOUT); also elsewhere on the board
/K_EN: R55.1; also elsewhere on the board
/K_SEL: R102.1; also elsewhere on the board
/MOTOR_COIL_NEG: J15.1, R111.2, R117.2
/MOTOR_COIL_POS: J15.2; also elsewhere on the board
/MOTOR_CONT_EN: R35.2; also elsewhere on the board
/MOTOR_CONT_FB: J15.4, R127.1; also elsewhere on the board
/PSU_SW_FAULT: J7.7; also elsewhere on the board
/PSU_SW_PGOOD: J7.6; also elsewhere on the board
/RS485_A: J12.3; also elsewhere on the board
/RS485_B: J12.4; also elsewhere on the board
/SCL: J7.8; also elsewhere on the board
/SDA: J7.4; also elsewhere on the board
/SOURCE_OV: R33.2; also elsewhere on the board
/SW_ARM: C56.1, R113.2, R119.2, U12.6 (3A)
/SW_ARM_BUF: U12.2 (3Y); also elsewhere on the board
/SW_COMPUTE: C55.1, R112.2, R118.2, U12.1 (1A)
/SW_COMPUTE_BUF: U12.7 (1Y); also elsewhere on the board
/SW_REMOTE_ARM: C58.1, R115.2, R121.2, U13.1 (1A)
/SW_REMOTE_ARM_BUF: U13.7 (1Y); also elsewhere on the board
/SW_REMOTE_DISARM: C59.1, R116.2, R122.2, U13.6 (3A)
/SW_REMOTE_DISARM_BUF: U13.2 (3Y); also elsewhere on the board
/SW_RST_FAULT: C57.1, R114.2, R120.2, U12.3 (2A)
/SW_RST_FAULT_BUF: U12.5 (2Y); also elsewhere on the board
/THERM_0: D36.1 (K), J17.2, R71.1; also elsewhere on the board
/THERM_1: D35.1 (K), J16.2, R70.1; also elsewhere on the board
/THERM_2: R69.1, TH1.1; also elsewhere on the board
/V_BUS: J13.4, J14.1
/V_BUS_DIV: C43.1, R80.2, R88.1; also elsewhere on the board
/V_BUS_POS: J18.4, R92.2; also elsewhere on the board
/V_NEG: J13.1, J13.2, K2.3 (N.O.)
/V_SENSE_NEG: C43.2, C44.2, J18.1, J18.3, R80.1, R81.1; also elsewhere on the board
/V_SOURCE: J13.3, K2.4 (N.C.)
/V_SOURCE_DIV: C44.1, R81.2, R89.1; also elsewhere on the board
/V_SOURCE_POS: J18.2, R101.2; also elsewhere on the board
GND: C13.2, C14.1, C15.1, C16.1, C18.1, C20.2, C21.2, C50.2, C51.2, C55.2, C56.2, C57.2, C58.2, C59.2, C60.1, C62.2, D5.1 (K), D6.1 (K), D7.1 (K), D8.1 (K), D9.1 (K), D11.1 (K), D13.1 (K), D14.1 (K), D15.1 (K), D16.1 (K), D17.1 (K), D18.1 (K), D20.1 (K), D21.1 (K), D23.1 (K), D30.2 (A), D31.2 (A), D32.2 (A), D33.2 (A), D34.2 (A), D37.2 (A), J1.1, J3.1, J4.1, J5.1, J6.1, J6.2, J6.3, J7.1, J7.2, J8.1, J8.2, J12.1, J21.1, NT1.2, Q1.2 (E), Q10.2 (E), Q14.2 (E), R6.1, R56.1, R103.1, R112.1, R113.1, R114.1, R115.1, R116.1, R123.1, R127.2, TP2.1, U5.2 (GND), U7.2 (GND_1), U7.4 (GND_2), U8.2 (GND), U12.4 (GND), U13.4 (GND); also elsewhere on the board
GNDA: C52.2, C54.2, C63.2, C64.1, D35.2 (A), D36.2 (A), J16.1, J17.1, NT1.1, TH1.2, TP3.1, U15.1 (VREF), U15.2 (VSS); also elsewhere on the board
unnamed: D5.2 (A), R5.1
unnamed: D6.2 (A), R9.1
unnamed: D7.2 (A), R18.1
unnamed: D8.2 (A), R27.1
unnamed: D9.2 (A), R28.1
unnamed: D11.2 (A), R30.1
unnamed: D13.2 (A), R33.1
unnamed: D14.2 (A), R34.1
unnamed: D15.2 (A), R35.1
unnamed: D16.2 (A), R39.1
unnamed: D17.2 (A), R41.1
unnamed: D18.2 (A), R42.1
unnamed: D19.2 (A), R43.1
unnamed: D19.1 (K), D24.1 (K), K1.5 (COIL_2), Q10.3 (C)
unnamed: D20.2 (A), R46.1
unnamed: D21.2 (A), R50.1, U5.5 (ST)
unnamed: D22.2 (A), D24.2 (A)
unnamed: D23.2 (A), R51.1
unnamed: D25.2 (A), R68.1
unnamed: D25.1 (K), D28.1 (K), K2.5 (COIL_2), Q14.3 (C)
unnamed: D26.2 (A), D28.2 (A)
unnamed: D30.1 (K), J20.4, R118.1
unnamed: D31.1 (K), J20.5, R119.1
unnamed: D32.1 (K), J20.6, R120.1
unnamed: D33.1 (K), J21.5, R121.1
unnamed: D34.1 (K), J21.6, R122.1
unnamed: D37.1 (K), J19.2, R125.1
unnamed: J2.1, U1.3
unnamed: J2.2, U1.4
unnamed: J15.3, R128.1
unnamed: J19.1, R129.2
unnamed: J20.1, R130.2
unnamed: J20.2, R131.2
unnamed: J20.3, R132.2
unnamed: J21.2, R126.2
unnamed: J21.3, R133.2
unnamed: K1.3 (NO), K2.1 (COM)
unnamed: Q1.1 (B), R6.2, R7.2
unnamed: Q1.3 (C), U1.2
unnamed: Q10.1 (B), R55.2, R56.2
unnamed: Q14.1 (B), R102.2, R103.2
unnamed: R8.2, U1.1
unnamed: R88.2, R92.1
unnamed: R89.2, R101.1
unnamed: R53.2, U5.3 (~CE), U8.5 (ST)
unnamed: C53.1, R110.1, U15.5 (VIM)
unnamed: C53.2, R117.1, U15.4 (VIP)

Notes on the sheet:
COMPARATORS
AUX OUTPUTS
CONNECTORS
MOUNTING
DIVIDERS
SWITCH INPUTS
ESTOP OUT
THERMISTORS
3.3V LDO
MISC TEST POINTS
POWER OR
MCU
MISC LEDS
FPGA
COIL DRIVER
DUMP/ PRECHARGE
